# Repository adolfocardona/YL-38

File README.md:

# YL-38
KiCad Sensor YL-38

Download Seeed OPL
https://github.com/Seeed-Studio/OPL_Kicad_Library

Download Pot 10K
https://www.seeedstudio.com/opl.html
Search -> 3362P-1-103LF

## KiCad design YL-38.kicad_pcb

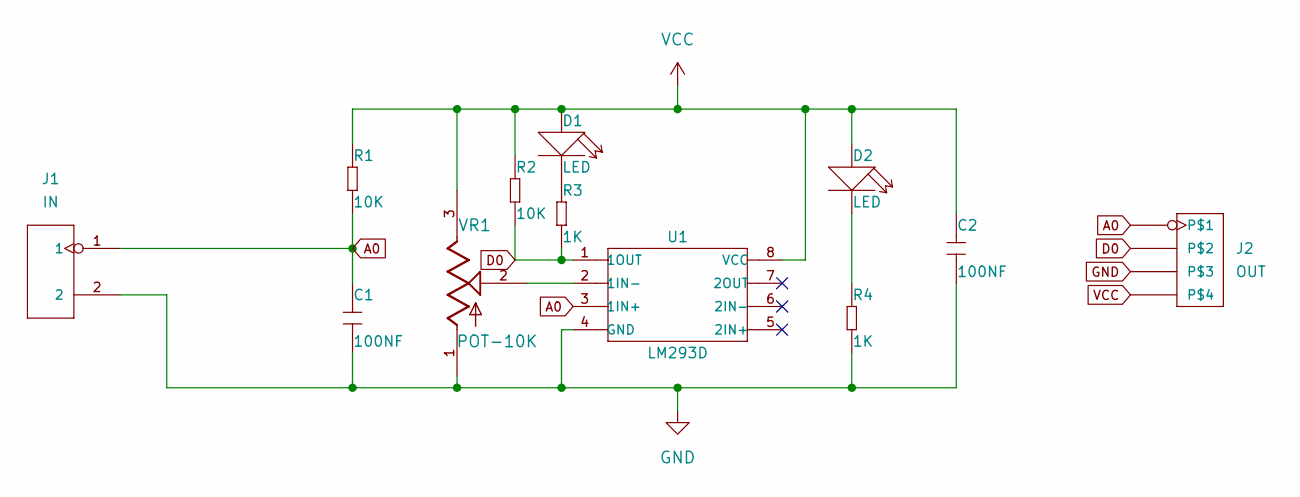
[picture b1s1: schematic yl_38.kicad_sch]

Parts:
C1, C2: 100NF; C0603; MPN CC0603KRX7R9BB104
D1, D2: LED; LED-0603; MPN 19-217-R6C-AL1M2VY-3T
J1: IN; H2-2.54; MPN P125-1102A0BS116A1
J2: OUT; H4-2.54; MPN P125-1104A0BS116A1
R1, R2: 10K; R0603; MPN RC0603FR-0710KL
R3, R4: 1K; R0603; MPN RC0603FR-071KL
U1: LM293D; SOIC8-1.27-5X4MM; MPN LM293D
VR1: POT-10K; TRIM_3362P-1-103LF; PARTREV 08/26/10

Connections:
A0: C1.2, J1.1, J2.1, R1.1, U1.3 (1IN+)
D0: J2.2, R2.1, R3.1, U1.1 (1OUT)
GND: C1.1, C2.1, J1.2, J2.3, R4.1, U1.4 (GND), VR1.1
unnamed: D1.2 (-), R3.2
unnamed: D2.2 (-), R4.2
unnamed: U1.2 (1IN-), VR1.2
VCC: C2.2, D1.1 (+), D2.1 (+), J2.4, R1.2, R2.2, U1.8 (VCC), VR1.3

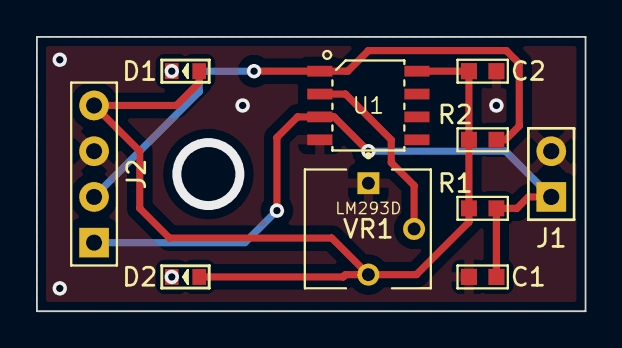
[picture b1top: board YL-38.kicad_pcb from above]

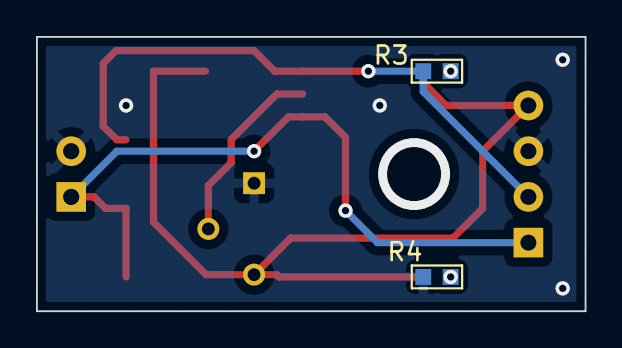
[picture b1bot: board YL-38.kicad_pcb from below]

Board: 2 copper layers, 30.5 x 15.2 mm, 12 parts (2 on the bottom side), 7 nets.
